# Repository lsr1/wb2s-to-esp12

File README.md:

# wb2s-to-esp12
passive pcb adapter-plate (drop-in replacement) for Tuya WB2S Wi-Fi Module to ESP12 Module

## Executive Summary
* This projects provides a drop-in replacement for a "[Tuya WB2S Wi-Fi <i>(sic!)</i> Module](https://developer.tuya.com/en/docs/iot/wb2s-module-datasheet?id=K9ghecl7kc479)". 
* This project consists of a KiCad project that gives you the Gerber files to order a PCB (e.g. at [JLCPCB](https://cart.jlcpcb.com)) onto which one ESP12 (flashed with the firmware of your choice), two switches and five 10k resistors are soldered. Then you remove the WB2S module and solder in your replacement module. <br>
* For the impatient: Go to [Installation](#Installation). 
* We did this for [these lamps](http://www.amazon.at/dp/B0767GB9NP).

## Picture

## Sidenotes
This is my first "public GitHub" project and thus neither very polished nor professional. I made something (crude) that I nevertheless think might be useful for somebody else. That is also the reason why this readme will be very long - for myself I want to document the story behind it for my records, and (hopefully) for your pleasure :-) </br>
Despite the verbosity of the README, it assumes that you know how to solder and some basic eletronics. Some things here are weirdly specific, while some are infuriating generic (assuming a lot of knowhow). 

## Preamble (Why)
A friend of a friend had WiFi enabled LED lights built into his house, and the electrician wired them to a normal mains switch. Every time he turned them on, 10+ lights got power and tried to connect to the WiFi AP. Some of them didn't get a connection and - default error behavour - started flashing. We (naively) just wanted to reflash [ESPHome](https://esphome.io/) (or [Tasmota](https://tasmota.github.io/docs/)), just to discover after opening the controller/PSU that no ESP but a WB2S module was built in - and those can't be flashed (yet?). Bummer! 

Long story short: We compared the voltages and signal pins - turns out these fit to an ESP! Since the module size reminded me of an ESP12 (and b/c I am a lazy person) I figured I'd just create a passive PCB with similar size as drop-in replacement.

## Pin-mapping
|row #| WB2S (pin)| ESP12 (pin)|
--- | --- | ---
|1|CEN (10)|EN (3)|
|2|AD (8) |ADC (2)|
|3|PWM0 (6) |GPIO4 (19)|
|4|PWM1 (4)|GPIO12 (6)|
|5|PWM2 (2) |GPIO13 (7)|
|6|VBAT (1)|VCC (8)|
|7|GND (3) |GND (15)|
|8|1RX (5) |RXD0 (21)|
|9|1TX (7)|TXD0 (22)|
|10|PWM4 (9)|GPIO5 (20)|
|11|PWM5 (11)|GPIO14 (5)|

## Design Decisions
* Size must not be (much) larger than the WB2S module (so that it fits in the housing of the [existing controller/PSU](photos/psu_controller.jpg))
* Drop-in replacement, thus all pins must retain the same position
* Utilize as many ESP pins as possible, despite the fact that the controller/PSU did not use all.
* Have a reset button (every IoT device needs one)
* Have a flash button (don't really know why.. but there was space left on the PCB, so why not)
* Because the PCB needed to be as small as possible, the pads for the ESP12 are cut off intentionally. There should be still enough area to get a solderjoint though. 

## BOM (for 1 module)
* 1 x PCB (see [Installation](#Installation)).
* 1 x ESP12 module
* 2 x switches (search for "SMD 3*6 *2.5 MM Tactile Tact Push Button Micro" on AliExpress)
* 5 x 0805 SMD 10k resistors

## Installation
* Get an ESP12 module and flash your preferred firmware and configure your WiFi. I used a device that you can find on AliExpress as "ESP12 burner". I'm writing this as first step b/c IMHO it's easier to flash  before you solder the ESP on the PCB (RX/TX is available, but why make your life compliated...). For future updates, OTA is availble in Tasmota and ESPhome. 
* Go to [JLCPCB](https://cart.jlcpcb.com/quote) and upload the [gerbers.zip](gerber/gerber.zip). Sidenote: I'm neither sponsored nor do I endorse them specifically, I just find them convenient. <b>Make sure you select the correct PCB thickness (0.8 mm).</b> I also set "Remove Order Number" to "Specify a location" (layout contains a field for this). No other special settings.
* Solder the components. I soldered the ESP12 first (try a reflow oven if you want to be fancy), b/c it provides a nice flat surface to lie on if flipped around for soldering the resistors and switches on the other side. 
* Check continuity of pads to ESP12 contacts with a multimeter (it's no fun to find out that one pad is not OK once the module is soldered in the mainboard).
* Solder the module into the mainboard of the controller/PSU.

## Software
* A friend of mine used this [ESPHome config](ESPhome/esplight.yaml) config.
* [WLED](https://github.com/Aircoookie/WLED) is also very cool. 

## Known 'bugs' (aka things that I plan to change for v0.2)
* The current version v0.1 shows the silkscreen for the courtyard of the switches on the wrong side (that's IMHO a bug in the component).
* The pads that stick "down through the mainboard" should be shorter (there is no harm if they are shorter, as they are only soldered from the bottom of the mainboard anyway) so that they are not that close to the ESP12 pads.
* Try to name the pads with silkscreen (3v3, GND, GPIOx, ...)
* Name the switches with silkscreen (SW1=RST and SW2=FLSH)

## License and Legalese
* May be (re)used for personal/private use only and not sold/licensed for commercial or financial gain. This non-standard license should make it impossible and really difficult for commercial enterprises to profit from my work (pay people to design this!), but enable the hobbyist/enthusiast to work with it. 
* I am using parts of the "SparkFun Electronics KiCad Libraries" which is licensed under the [Creative Commons Attribution 4.0 International](https://creativecommons.org/licenses/by/4.0/) license. 
* If I have inadverently (re-)used your work without either properly attributing it or something, please let me know - I'd be happy to correct this.

## Donations
Yes please.

## Feedback
Also yes please! (I hope I figure out how this whole pull-request thing works...)

## Shoutout ...
* ... to [CCC](https://www.ccc.de) and [CCCZH](https://www.ccczh.ch/)!
* ... to all FOSS contributors that helped making SW that enabled me to do this. Nanos gigantium humeris insidentes.

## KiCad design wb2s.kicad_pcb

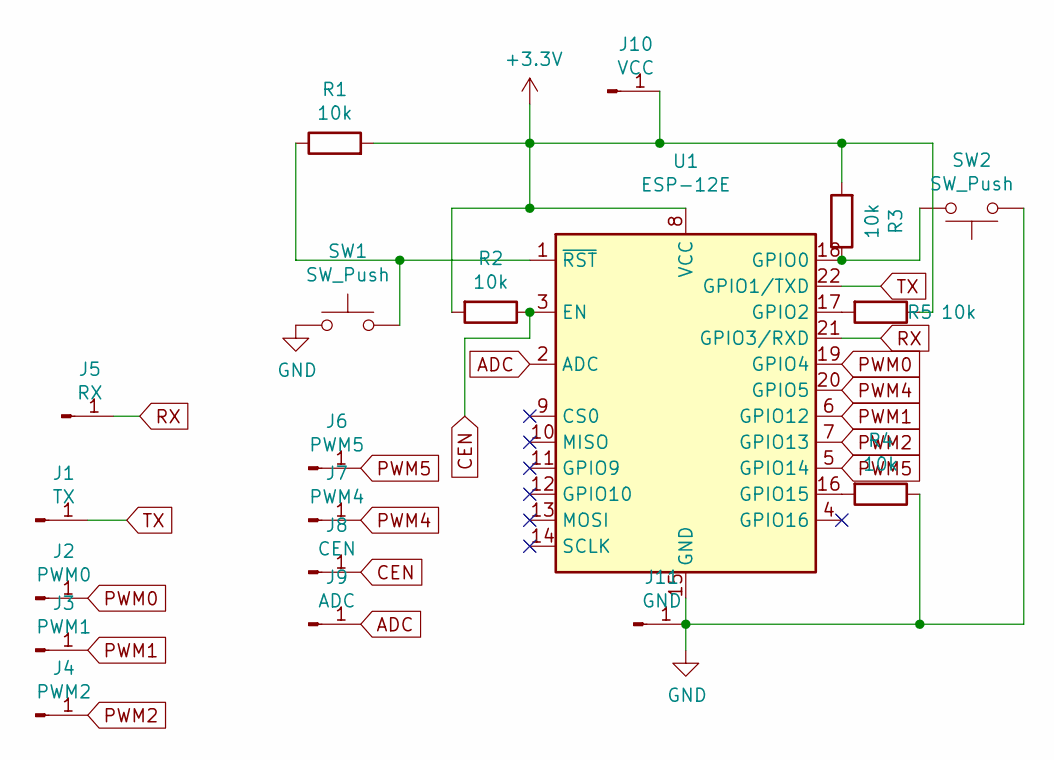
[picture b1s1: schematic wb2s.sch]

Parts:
J1: TX; TestPoint_Pad_1.0x2.0mm
J2: PWM0; TestPoint_Pad_1.0x2.0mm
J3: PWM1; TestPoint_Pad_1.0x2.0mm
J4: PWM2; TestPoint_Pad_1.0x2.0mm
J5: RX; TestPoint_Pad_1.0x2.0mm
J6: PWM5; TestPoint_Pad_1.0x2.0mm
J7: PWM4; TestPoint_Pad_1.0x2.0mm
J8: CEN; TestPoint_Pad_1.0x2.0mm
J9: ADC; TestPoint_Pad_1.0x2.0mm
J10: VCC; TestPoint_Pad_1.0x2.0mm
J11: GND; TestPoint_Pad_1.0x2.0mm
R1, R2, R3, R4: 10k; R_0805_2012Metric_Pad1.20x1.40mm_HandSolder
R5: 10k; R_0805_2012Metric_Pad1.15x1.40mm_HandSolder
SW1, SW2: SW_Push; TACTILE-SWITCH-1101NE
U1: ESP-12E

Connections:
+3V3: J10.1, R1.2, R2.2, R3.2, R5.1, U1.8 (VCC)
ADC: J9.1, U1.2 (ADC)
CEN: J8.1, R2.1, U1.3 (EN)
GND: J11.1, R4.1, SW1.1, SW2.1, U1.15 (GND)
unnamed: R1.1, SW1.2, U1.1 (~RST)
unnamed: R3.1, SW2.2, U1.18 (GPIO0)
unnamed: R4.2, U1.16 (GPIO15)
unnamed: R5.2, U1.17 (GPIO2)
PWM0: J2.1, U1.19 (GPIO4)
PWM1: J3.1, U1.6 (GPIO12)
PWM2: J4.1, U1.7 (GPIO13)
PWM4: J7.1, U1.20 (GPIO5)
PWM5: J6.1, U1.5 (GPIO14)
RX: J5.1, U1.21 (GPIO3/RXD)
TX: J1.1, U1.22 (GPIO1/TXD)

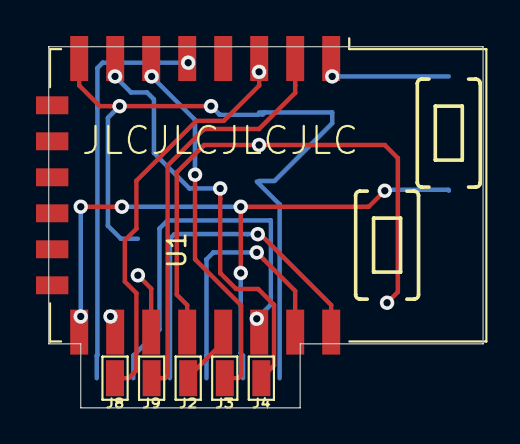
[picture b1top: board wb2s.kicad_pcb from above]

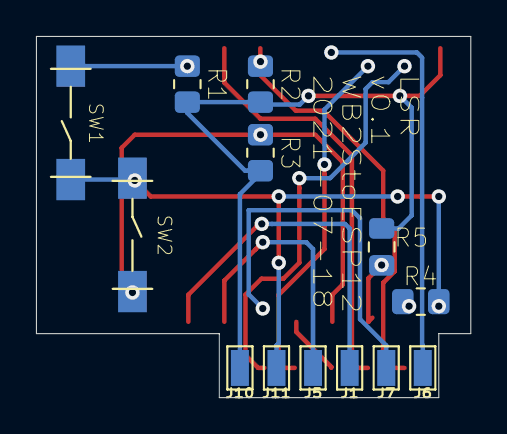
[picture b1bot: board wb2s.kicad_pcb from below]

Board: 2 copper layers, 24.1 x 20.1 mm, 19 parts (13 on the bottom side), 15 nets.

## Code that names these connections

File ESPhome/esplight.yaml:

substitutions:
  DeviceName: esplight
  
esphome:
  name: $DeviceName
  platform: ESP8266
  board: esp01_1m
  
<<: !include common/home_wifi.yaml
  #<<: !include common/home_mqtt.yaml
  
api:

#logger:

web_server:
  port: 80

# Example configuration entry
light:
    - platform: rgbww
      name: "Test Lights"
      red: light_r
      green: light_g
      blue: light_b
      cold_white: light_cw
      warm_white: light_ww
      cold_white_color_temperature: 6536 K
      warm_white_color_temperature: 2000 K
      color_interlock: false
      effects:
        - pulse:
            name: "Pulse"
        - strobe:
            name: "Panic!"
        - flicker:
            name: "Flicker"


# Example output entry
output:
    - platform: esp8266_pwm
      id: light_cw
      frequency: 1000 Hz
      pin: GPIO14
      
    - platform: esp8266_pwm
      id: light_g
      frequency: 1000 Hz
      pin: GPIO12

    - platform: esp8266_pwm
      id: light_b
      frequency: 1000 Hz
      pin: GPIO4

    - platform: esp8266_pwm
      id: light_ww
      frequency: 1000 Hz
      pin: GPIO5

    - platform: esp8266_pwm
      id: light_r
      frequency: 1000 Hz
      pin: GPIO13

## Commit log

2021-09-12 modified .gitignore
2021-09-12 cleanup
2021-09-12 cleanup 2
2021-09-12 added pcb pic
2021-09-12 removed wrong pics
2021-09-12 updated .gitignore
2021-09-12 added controller pictures
2021-09-12 added pictures and pinmapping
2021-09-12 readme link
2021-09-12 readme update
2021-09-12 various
2022-01-20 fixed readme
2022-01-20 removed orphaned file
